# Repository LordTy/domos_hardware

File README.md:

domos_hardware
==============

Kicad Pojects for domos hardware

modules
=======

This project contains all the hardware designs for the domos system. It contains the following modules:

 *  CC2538_module,  a core module with an ARM processor and wireless capabilities, xbee compatible.

folder structure
================
Every module has its own folder and kicad project.
The shared libraries, footprints and models are stored in: lib, mod and dcm respectively.

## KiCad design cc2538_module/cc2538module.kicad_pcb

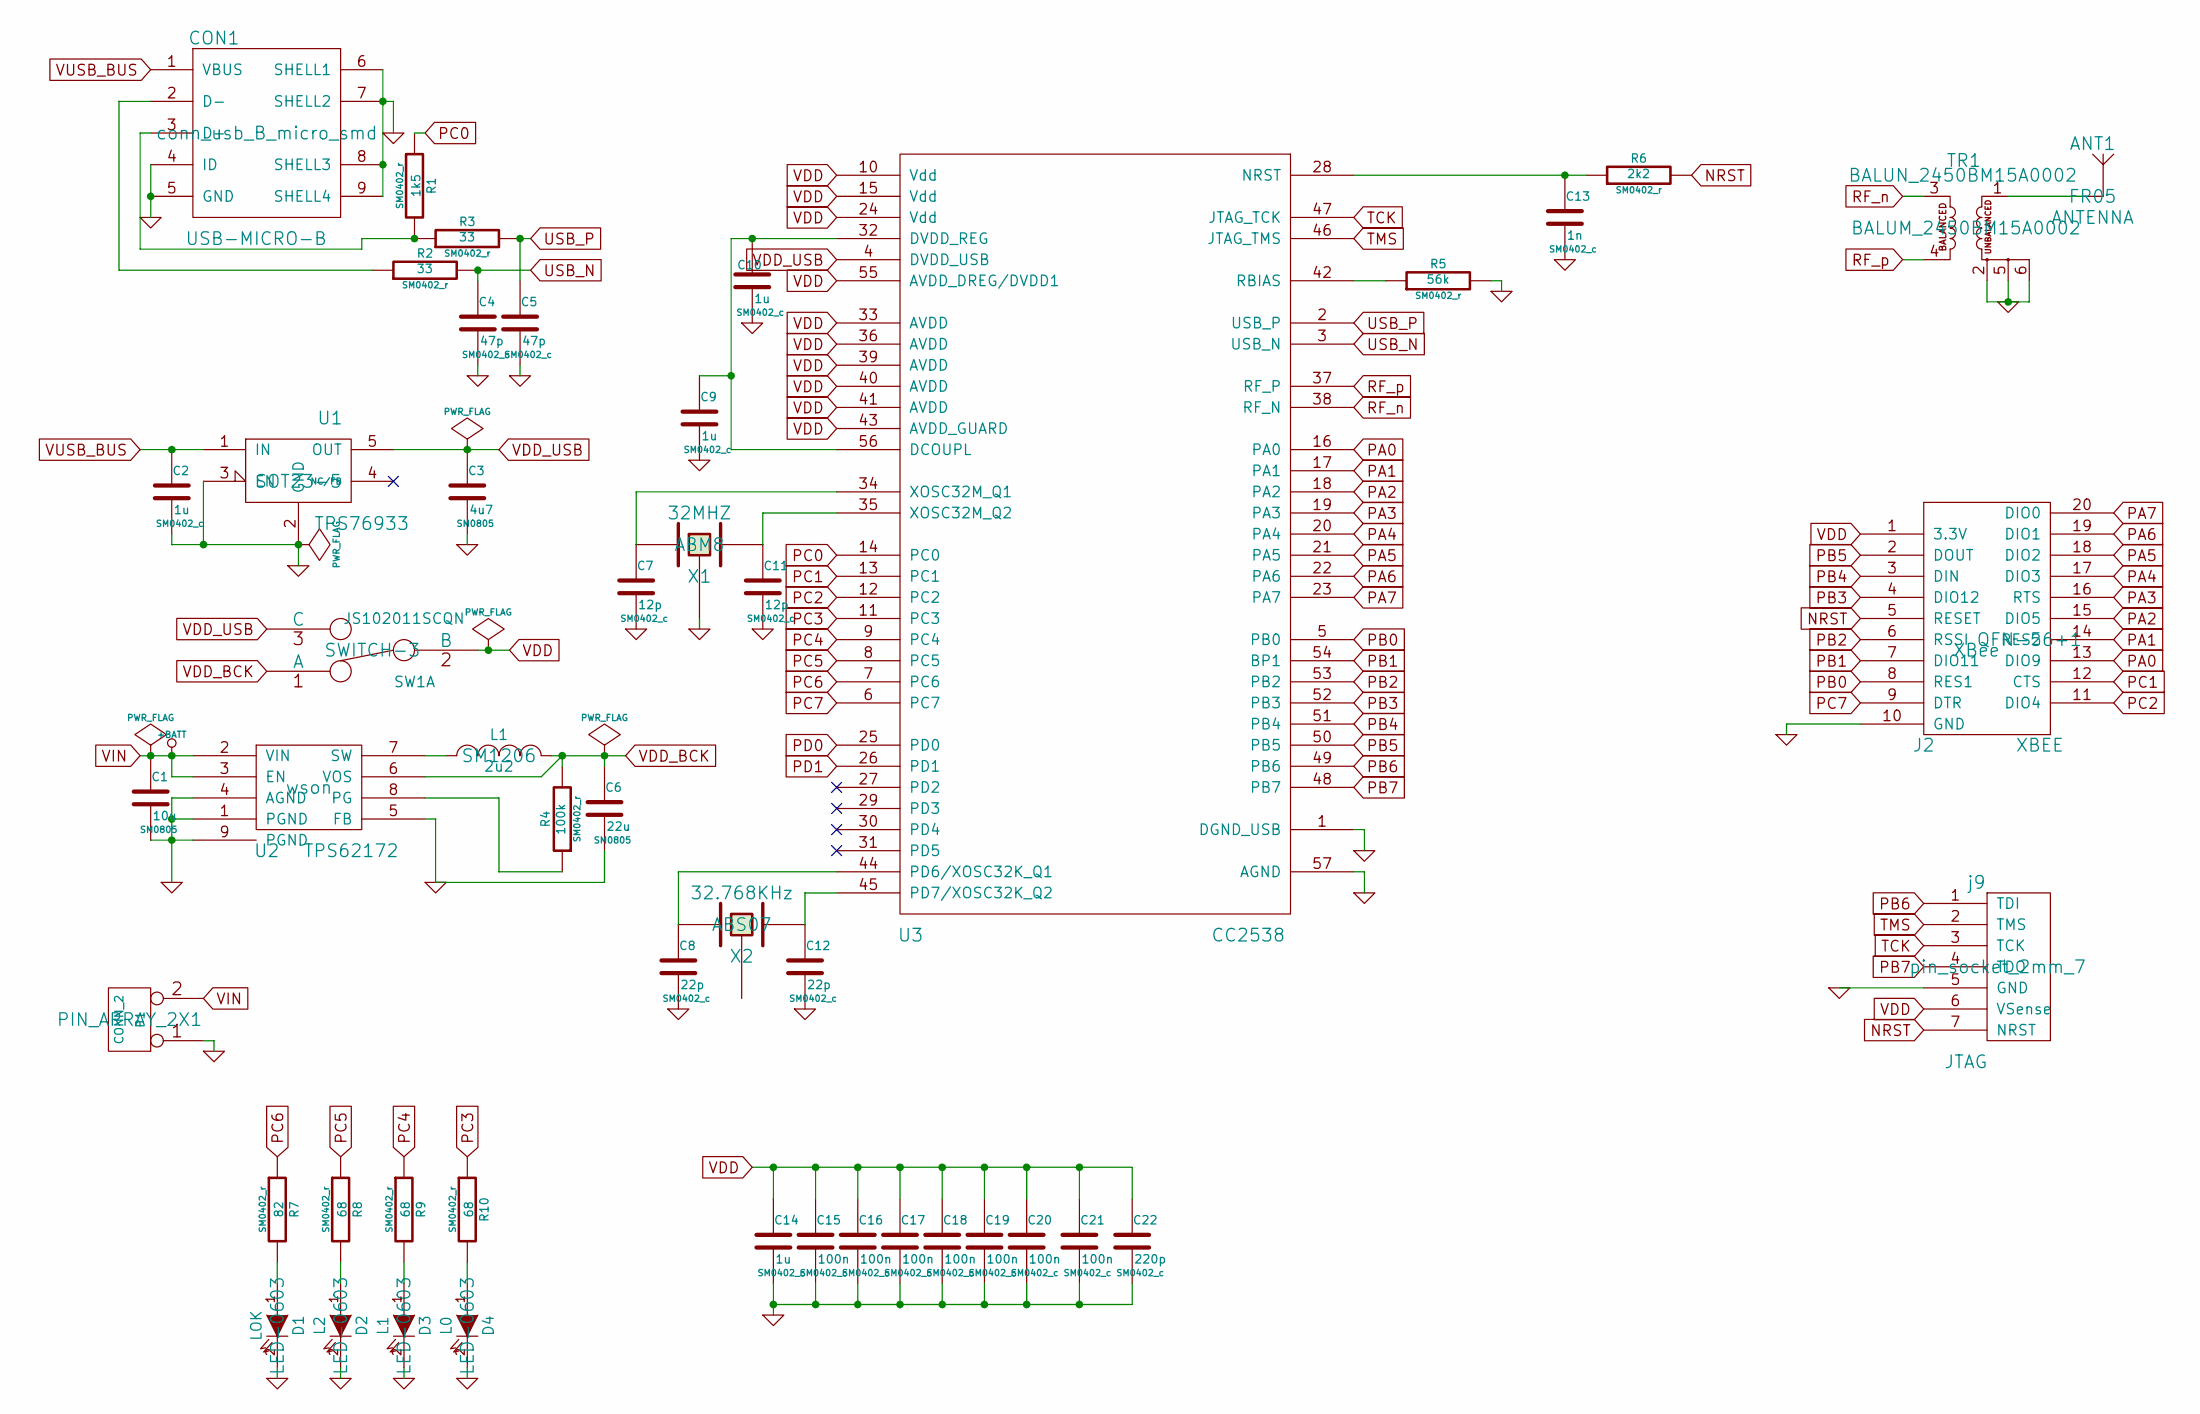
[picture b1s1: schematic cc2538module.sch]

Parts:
ANT1: ANTENNA; FR05
C1: 10u; SM0805; Voltage 12
C2: 1u; SM0402_c; Voltage 5
C3: 4u7; SM0805; Voltage 3.3
C4, C5: 47p; SM0402_c; Voltage 5
C6: 22u; SM0805; Voltage 3.3
C7, C11: 12p; SM0402_c; Voltage 3.3
C8, C12: 22p; SM0402_c; Voltage 3.3
C9, C10, C14: 1u; SM0402_c; Voltage 3.3
C13: 1n; SM0402_c; Voltage 3.3
C15, C16, C17, C18, C19, C20, C21: 100n; SM0402_c; Voltage 3.3
C22: 220p; SM0402_c; Voltage 3.3
CON1: USB-MICRO-B; conn_usb_B_micro_smd
D1: LOK; LED-0603; Voltage ~1.6
D2: L2; LED-0603; Voltage 2
D3: L1; LED-0603; Voltage 2
D4: L0; LED-0603; Voltage 2
J2: XBEE; XBee
L1: 2u2; SM1206
P1: CONN_2; PIN_ARRAY_2X1
R1: 1k5; SM0402_r
R2, R3: 33; SM0402_r
R4: 100k; SM0402_r
R5: 56k; SM0402_r
R6: 2k2; SM0402_r
R7: 82; SM0402_r
R8, R9, R10: 68; SM0402_r
SW1: JS102011SCQN; SWITCH-3
TR1: BALUN_2450BM15A0002; BALUM_2450BM15A0002
U1: TPS76933; SOT23-5; Voltage 3.3
U2: TPS62172; wson; Voltage 3.3
U3: CC2538; QFN-56+1
X1: 32MHZ; ABM8
X2: 32.768KHz; ABS07
j9: JTAG; pin_socket_2mm_7

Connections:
GND: C1.2, C2.2, C3.2, C4.2, C5.2, C6.2, C7.2, C8.2, C9.2, C10.2, C11.2, C12.2, C13.2, C14.2, C15.2, C16.2, C17.2, C18.2, C19.2, C20.2, C21.2, C22.2, CON1.4 (ID), CON1.5 (GND), CON1.6 (SHELL1), CON1.7 (SHELL2), CON1.8 (SHELL3), CON1.9 (SHELL4), D1.2 (K), D2.2 (K), D3.2 (K), D4.2 (K), J2.10 (GND), P1.1, R5.2, TR1.2, TR1.5, TR1.6, U1.2 (GND), U1.3 (EN), U2.1 (PGND), U2.4 (AGND), U2.5 (FB), U2.9 (PGND), U3.1 (DGND_USB), U3.57 (AGND), X1.3 (gnd), j9.5 (GND)
unnamed: CON1.3 (D+), R1.2, R3.1
unnamed: C12.1, U3.45 (PD7/XOSC32K_Q2), X2.2
unnamed: R5.1, U3.42 (RBIAS)
unnamed: C8.1, U3.44 (PD6/XOSC32K_Q1), X2.1
unnamed: C7.1, U3.34 (XOSC32M_Q1), X1.1
unnamed: C11.1, U3.35 (XOSC32M_Q2), X1.2
unnamed: CON1.2 (D-), R2.1
unnamed: D4.1 (A), R10.2
unnamed: D3.1 (A), R9.2
unnamed: D2.1 (A), R8.2
unnamed: D1.1 (A), R7.2
unnamed: R4.1, U2.8 (PG)
unnamed: L1.1, U2.7 (SW)
unnamed: ANT1.1, TR1.1
unnamed: C13.1, R6.1, U3.28 (NRST)
unnamed: C9.1, C10.1, U3.32 (DVDD_REG), U3.56 (DCOUPL)
NRST: J2.5 (RESET), R6.2, j9.7 (NRST)
PA0: J2.13 (DIO9), U3.16 (PA0)
PA1: J2.14 (RES2), U3.17 (PA1)
PA2: J2.15 (DIO5), U3.18 (PA2)
PA3: J2.16 (RTS), U3.19 (PA3)
PA4: J2.17 (DIO3), U3.20 (PA4)
PA5: J2.18 (DIO2), U3.21 (PA5)
PA6: J2.19 (DIO1), U3.22 (PA6)
PA7: J2.20 (DIO0), U3.23 (PA7)
PB0: J2.8 (RES1), U3.5 (PB0)
PB1: J2.7 (DIO11), U3.54 (BP1)
PB2: J2.6 (RSSI), U3.53 (PB2)
PB3: J2.4 (DIO12), U3.52 (PB3)
PB4: J2.3 (DIN), U3.51 (PB4)
PB5: J2.2 (DOUT), U3.50 (PB5)
PB6: U3.49 (PB6), j9.1 (TDI)
PB7: U3.48 (PB7), j9.4 (TDO)
PC0: R1.1, U3.14 (PC0)
PC1: J2.12 (CTS), U3.13 (PC1)
PC2: J2.11 (DIO4), U3.12 (PC2)
PC3: R10.1, U3.11 (PC3)
PC4: R9.1, U3.9 (PC4)
PC5: R8.1, U3.8 (PC5)
PC6: R7.1, U3.7 (PC6)
PC7: J2.9 (DTR), U3.6 (PC7)
RF_n: TR1.3, U3.38 (RF_N)
RF_p: TR1.4, U3.37 (RF_P)
TCK: U3.47 (JTAG_TCK), j9.3 (TCK)
TMS: U3.46 (JTAG_TMS), j9.2 (TMS)
USB_N: C4.1, R2.2, U3.3 (USB_N)
USB_P: C5.1, R3.2, U3.2 (USB_P)
VDD: C14.1, C15.1, C16.1, C17.1, C18.1, C19.1, C20.1, C21.1, C22.1, J2.1 (3.3V), SW1.2 (B), U3.10 (Vdd), U3.15 (Vdd), U3.24 (Vdd), U3.33 (AVDD), U3.36 (AVDD), U3.39 (AVDD), U3.40 (AVDD), U3.41 (AVDD), U3.43 (AVDD_GUARD), U3.55 (AVDD_DREG/DVDD1), j9.6 (VSense)
VDD_BCK: C6.1, L1.2, R4.2, SW1.1 (A), U2.6 (VOS)
VDD_USB: C3.1, SW1.3 (C), U1.5 (OUT), U3.4 (DVDD_USB)
VIN: C1.1, P1.2 (PM), U2.2 (VIN), U2.3 (EN)
VUSB_BUS: C2.1, CON1.1 (VBUS), U1.1 (IN)

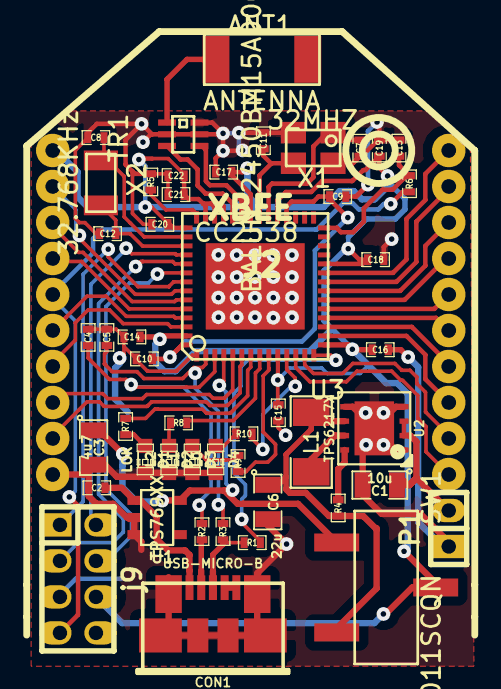
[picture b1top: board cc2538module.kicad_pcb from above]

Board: 2 copper layers, 49 parts (0 on the bottom side), 53 nets.

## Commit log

2014-07-30 Added cc2538 module and lib and mod files
2014-07-30 added .gitignore for kicad .bac and .bck files
2014-08-01 fixed some more routing to the pcb
2014-08-01 Finished top half of the PCB
2014-08-01 Update component tolerances
2014-08-01 Finisched layouting board
2014-08-01 Moved usb connector to pcb edge
